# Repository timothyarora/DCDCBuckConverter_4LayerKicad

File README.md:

I crafted the 4-Layer PCB layout for the NB679 Buck Converter using KiCad, making effective use of both the Schematic Editor and PCB Editor. I meticulously designed custom symbols and footprints, adhering closely to the NB679 datasheet to ensure precision and optimization in the circuit layout.

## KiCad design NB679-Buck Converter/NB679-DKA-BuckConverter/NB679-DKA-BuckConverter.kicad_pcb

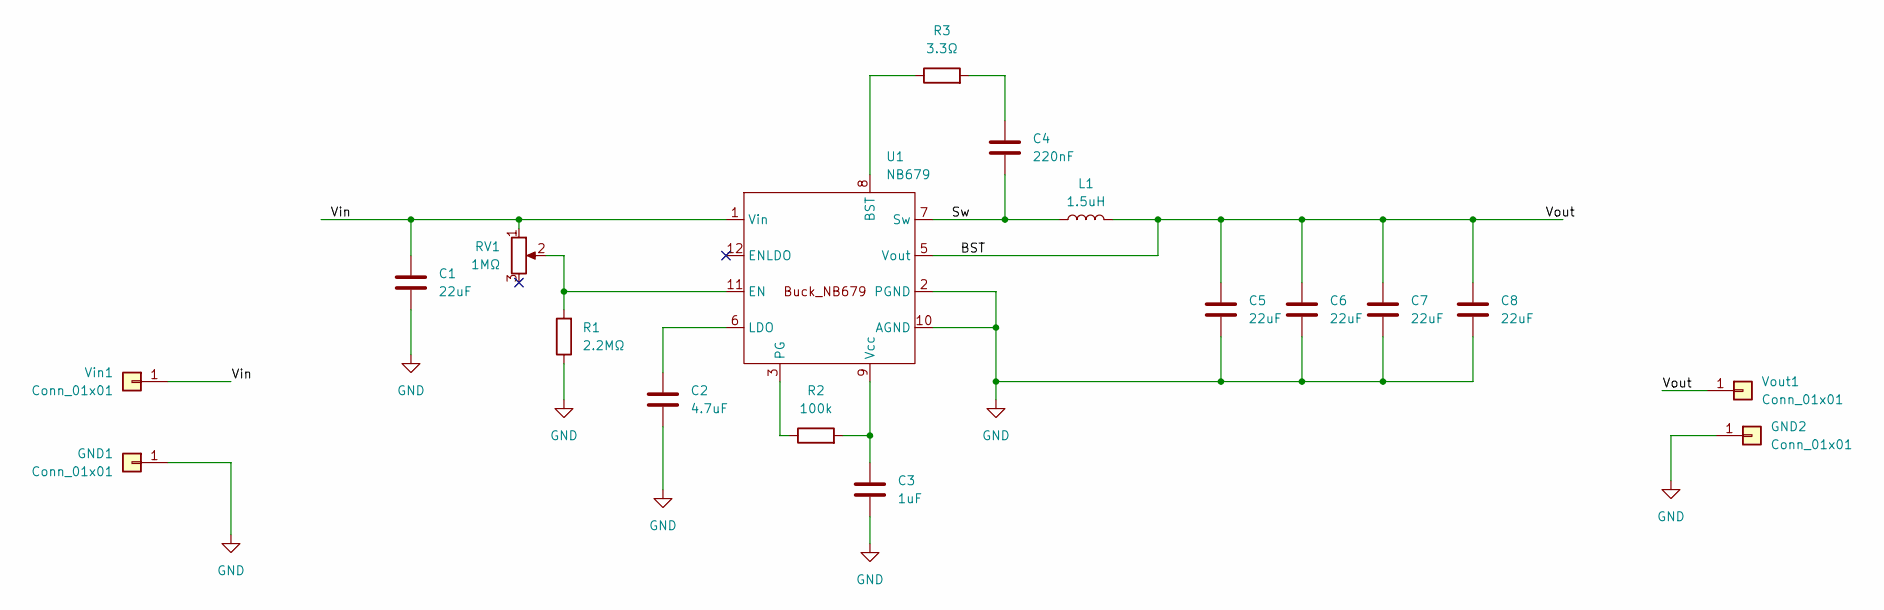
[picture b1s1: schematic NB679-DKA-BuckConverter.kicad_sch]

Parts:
C1, C5, C6, C7, C8: 22uF; C_0805_2012Metric_Pad1.18x1.45mm_HandSolder
C2: 4.7uF; C_0603_1608Metric_Pad1.08x0.95mm_HandSolder
C3: 1uF; C_0402_1005Metric_Pad0.74x0.62mm_HandSolder
C4: 220nF; C_0402_1005Metric_Pad0.74x0.62mm_HandSolder
GND1, GND2: Conn_01x01; PinHeader_1x01_P2.54mm_Vertical
L1: 1.5uH; IND_FP
R1: 2.2MΩ; R_0805_2012Metric_Pad1.20x1.40mm_HandSolder
R2: 100k; R_1206_3216Metric_Pad1.30x1.75mm_HandSolder
R3: 3.3Ω; R_1206_3216Metric_Pad1.30x1.75mm_HandSolder
RV1: 1MΩ; POT_FP
U1: NB679; IC_NB679_FP
Vin1: Conn_01x01; PinHeader_1x01_P2.54mm_Vertical
Vout1: Conn_01x01; PinHeader_1x01_P2.54mm_Vertical

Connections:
/BST: C5.1, C6.1, C7.1, C8.1, L1.2, U1.5 (Vout), Vout1.1
/Sw: C4.2, L1.1, U1.7 (Sw)
/Vin: C1.1, RV1.1, U1.1 (Vin), Vin1.1
GND: C1.2, C2.2, C3.2, C5.2, C6.2, C7.2, C8.2, GND1.1, GND2.1, R1.1, U1.2 (PGND), U1.10 (AGND)
unnamed: C4.1, R3.2
unnamed: R3.1, U1.8 (BST)
unnamed: R1.2, RV1.2, U1.11 (EN)
unnamed: C2.1, U1.6 (LDO)
unnamed: R2.1, U1.3 (PG)
unnamed: C3.1, R2.2, U1.9 (Vcc)

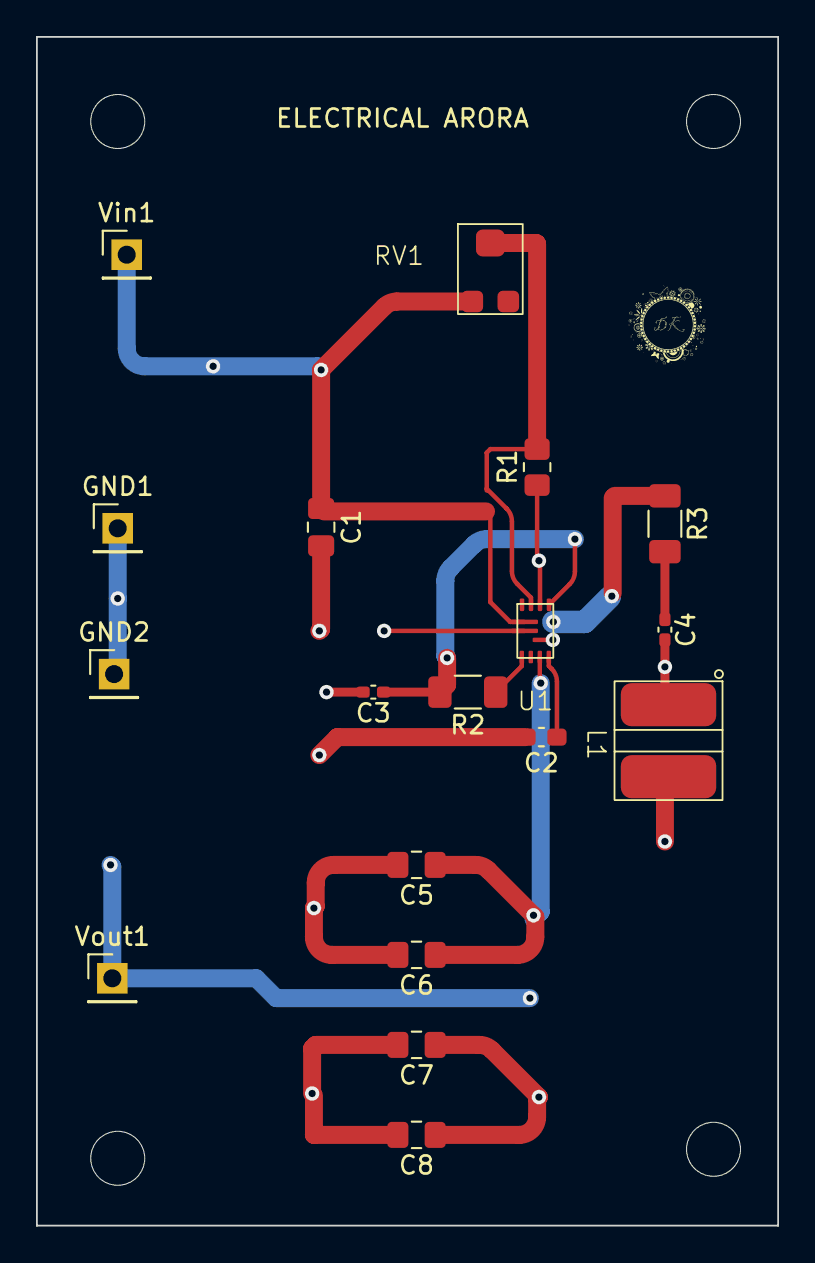
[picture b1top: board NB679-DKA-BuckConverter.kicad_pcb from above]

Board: 4 copper layers, 41.2 x 66.0 mm, 18 parts (0 on the bottom side), 10 nets.

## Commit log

2023-11-20 Revert "Add files via upload"
    This reverts commit f3abc6e5cdbc4eb3a7c27640f7560002a22d9b6a.
2023-11-20 Revert "Revert "Add files via upload""
    This reverts commit 97fd2a391e5fb4800b3cd6add9f81a7e8c48e4bc.
2023-11-20 Buck Converter NB679
    KiCad 4 Layer Project for NB679 Buck Converter
